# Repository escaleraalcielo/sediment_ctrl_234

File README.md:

# sediment_ctrl_234
 Repositorio en Github con todo el contenido relacionado con el rediseño de la trampa de sediemntos S/MT 234

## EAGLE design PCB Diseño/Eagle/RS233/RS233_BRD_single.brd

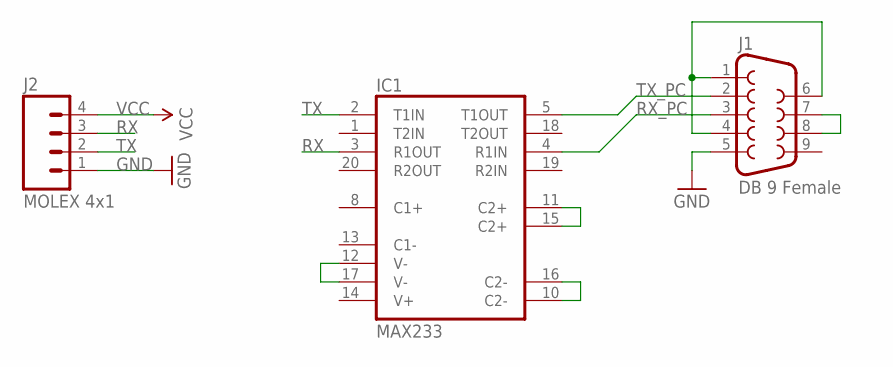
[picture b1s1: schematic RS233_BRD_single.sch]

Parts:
IC1: MAX233; DIL20
J1: DB 9 Female; DB9
J2: MOLEX 4x1; MOLEX-1X4

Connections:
GND: IC1.6 (GND), IC1.9 (GND), J1.5, J2.1
unnamed: IC1.11 (C2+), IC1.15 (C2+)
unnamed: IC1.10 (C2-), IC1.16 (C2-)
unnamed: J1.7, J1.8
unnamed: J1.1, J1.4, J1.6
unnamed: IC1.12 (V-), IC1.17 (V-)
RX: IC1.3 (R1OUT), J2.3
RX_PC: IC1.4 (R1IN), J1.3
TX: IC1.2 (T1IN), J2.2
TX_PC: IC1.5 (T1OUT), J1.2
VCC: IC1.7 (VCC), J2.4

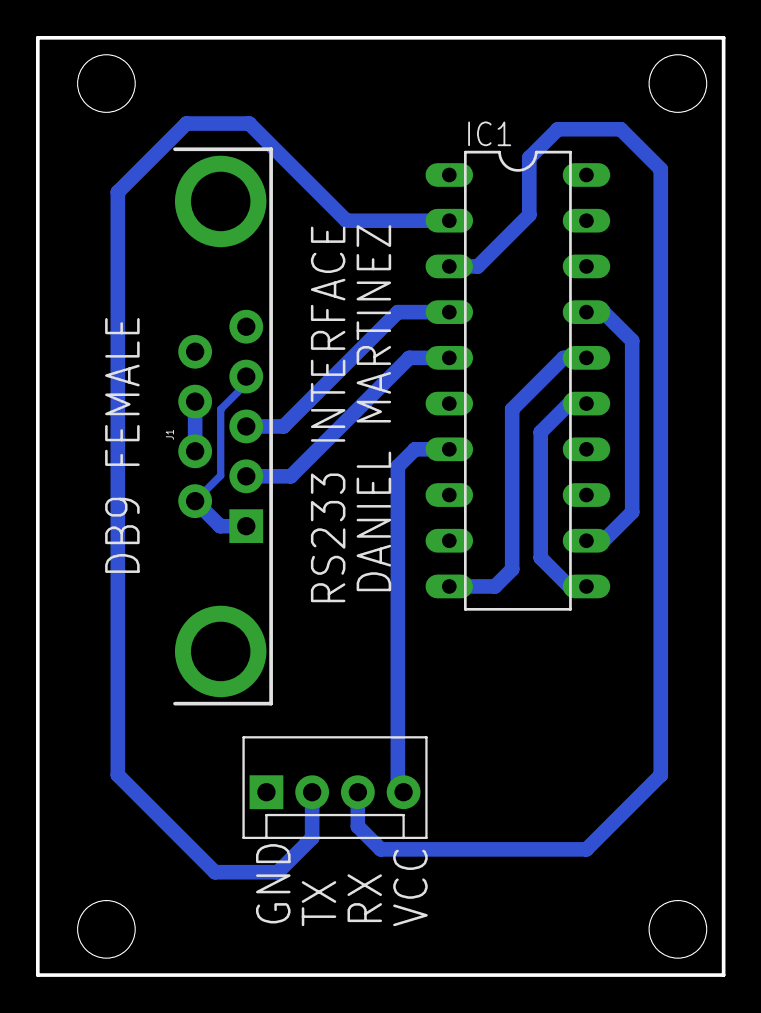
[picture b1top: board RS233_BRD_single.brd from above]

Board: 2 copper layers, 38.1 x 52.1 mm, 3 parts (0 on the bottom side), 11 nets.

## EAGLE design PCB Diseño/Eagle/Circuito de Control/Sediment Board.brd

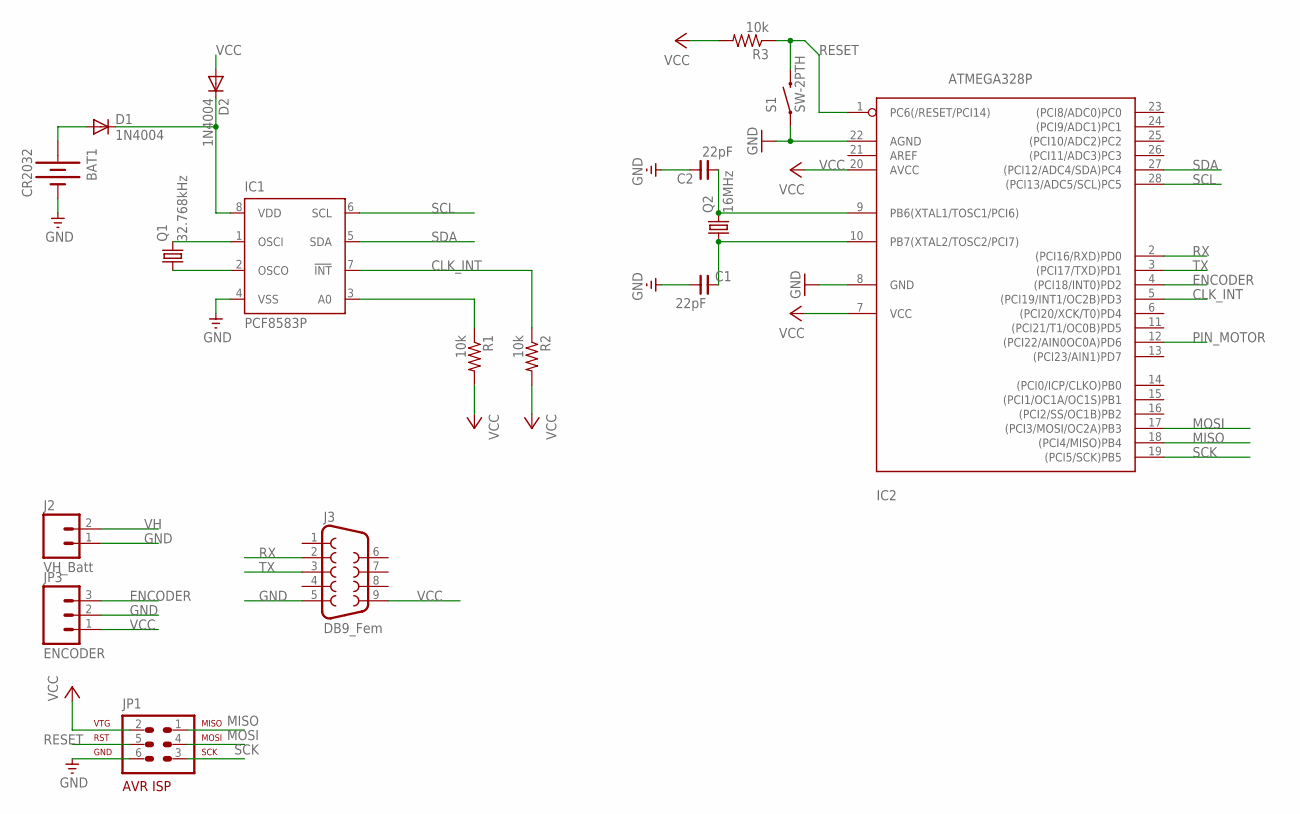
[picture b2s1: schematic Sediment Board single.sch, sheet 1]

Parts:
BAT1: CR2032; BATTCOM_20MM_PTH
C1, C2: 22pF; C025-050X025
D1, D2: 1N4004; DO41-10
IC1: PCF8583P; DIL08
IC2: ATMEGA328P; DIL28-3-ROUND
J2: VH_Batt; SCREWTERMINAL-3.5MM-2
J3: DB9_Fem; DB9
JP1: AVR-ISP-6
JP3: ENCODER; MOLEX-1X3
Q1: 32.768kHz; TC26H
Q2: 16MHz; HC49U70
R1, R2, R3: 10k; 0207/10
S1: SW-2PTH; TACTILE-PTH

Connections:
CLK_INT: IC1.7 (!INT), IC2.5 ((PCI19/INT1/OC2B)PD3), R2.1
ENCODER: IC2.4 ((PCI18/INT0)PD2), JP3.3
GND: BAT1.2 (-), C1.1, C2.2, IC1.4 (VSS), IC2.8 (GND), IC2.22 (AGND), J2.1, J3.5, JP1.6, JP3.2, S1.1; also elsewhere on the board
MISO: IC2.18 ((PCI4/MISO)PB4), JP1.1
MOSI: IC2.17 ((PCI3/MOSI/OC2A)PB3), JP1.4
unnamed: D1.C, D2.C, IC1.8 (VDD)
unnamed: IC1.1 (OSCI), Q1.2
unnamed: IC1.2 (OSCO), Q1.1
unnamed: BAT1.1 (+), D1.A
unnamed: IC1.3 (A0), R1.1
unnamed: C2.1, IC2.9 (PB6(XTAL1/TOSC1/PCI6)), Q2.2
unnamed: C1.2, IC2.10 (PB7(XTAL2/TOSC2/PCI7)), Q2.1
PIN_MOTOR: IC2.12 ((PCI22/AIN0OC0A)PD6); also elsewhere on the board
RESET: IC2.1 (PC6(/RESET/PCI14)), JP1.5, R3.1, S1.3 (2)
RX: IC2.2 ((PCI16/RXD)PD0), J3.2
SCK: IC2.19 ((PCI5/SCK)PB5), JP1.3
SCL: IC1.6 (SCL), IC2.28 ((PCI13/ADC5/SCL)PC5)
SDA: IC1.5 (SDA), IC2.27 ((PCI12/ADC4/SDA)PC4)
TX: IC2.3 ((PCI17/TXD)PD1), J3.3
VCC: D2.A, IC2.7 (VCC), IC2.20 (AVCC), J3.9, JP1.2, JP3.1, R1.2, R2.2, R3.2; also elsewhere on the board
VH: J2.2; also elsewhere on the board

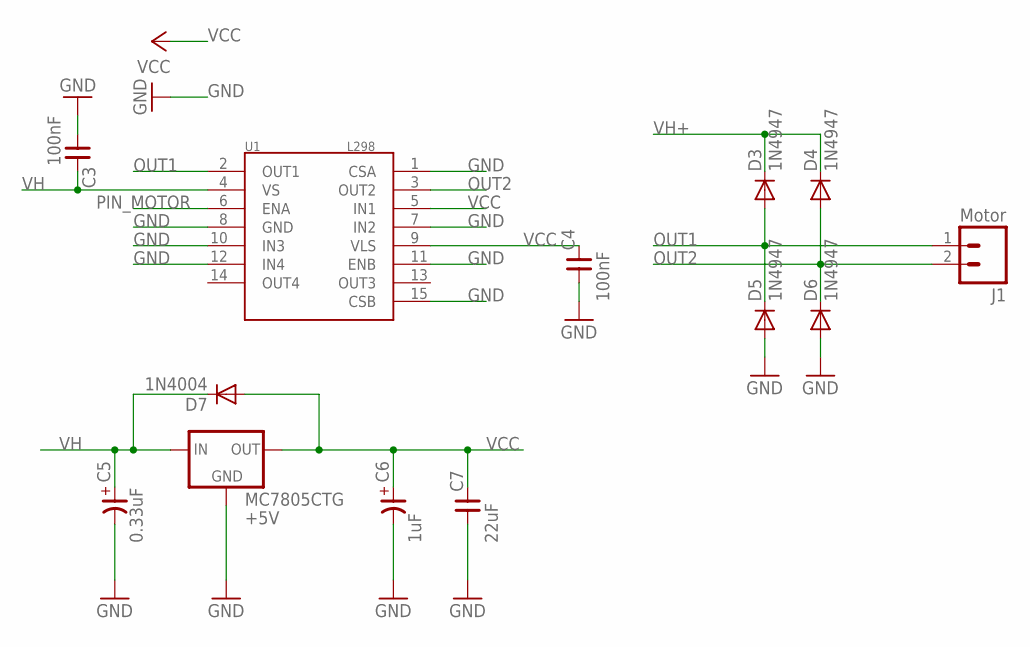
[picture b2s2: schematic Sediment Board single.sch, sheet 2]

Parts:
C3, C4: 100nF; C025-050X025
C5: 0.33uF; TT-025-040
C6: 1uF; TT-025-040
C7: 22uF; C025-050X025
D3, D4, D5, D6: 1N4947; DO41-10
D7: 1N4004; DO41-10
J1: Motor; SCREWTERMINAL-3.5MM-2
MC7805CTG: +5V; 78XXL
U1: L298; MULTIWATT15

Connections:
GND: C3.1, C4.1, C5.-, C6.-, C7.1, D5.A, D6.A, MC7805CTG.GND, U1.1 (CSA), U1.7 (IN2), U1.8 (GND), U1.10 (IN3), U1.11 (ENB), U1.12 (IN4), U1.15 (CSB); also elsewhere on the board
OUT1: D3.A, D5.C, J1.1, U1.2 (OUT1)
OUT2: D4.A, D6.C, J1.2, U1.3 (OUT2)
PIN_MOTOR: U1.6 (ENA); also elsewhere on the board
VCC: C4.2, C6.+, C7.2, D7.A, MC7805CTG.OUT, U1.5 (IN1), U1.9 (VLS); also elsewhere on the board
VH: C3.2, C5.+, D7.C, MC7805CTG.IN, U1.4 (VS); also elsewhere on the board
VH+: D3.C, D4.C

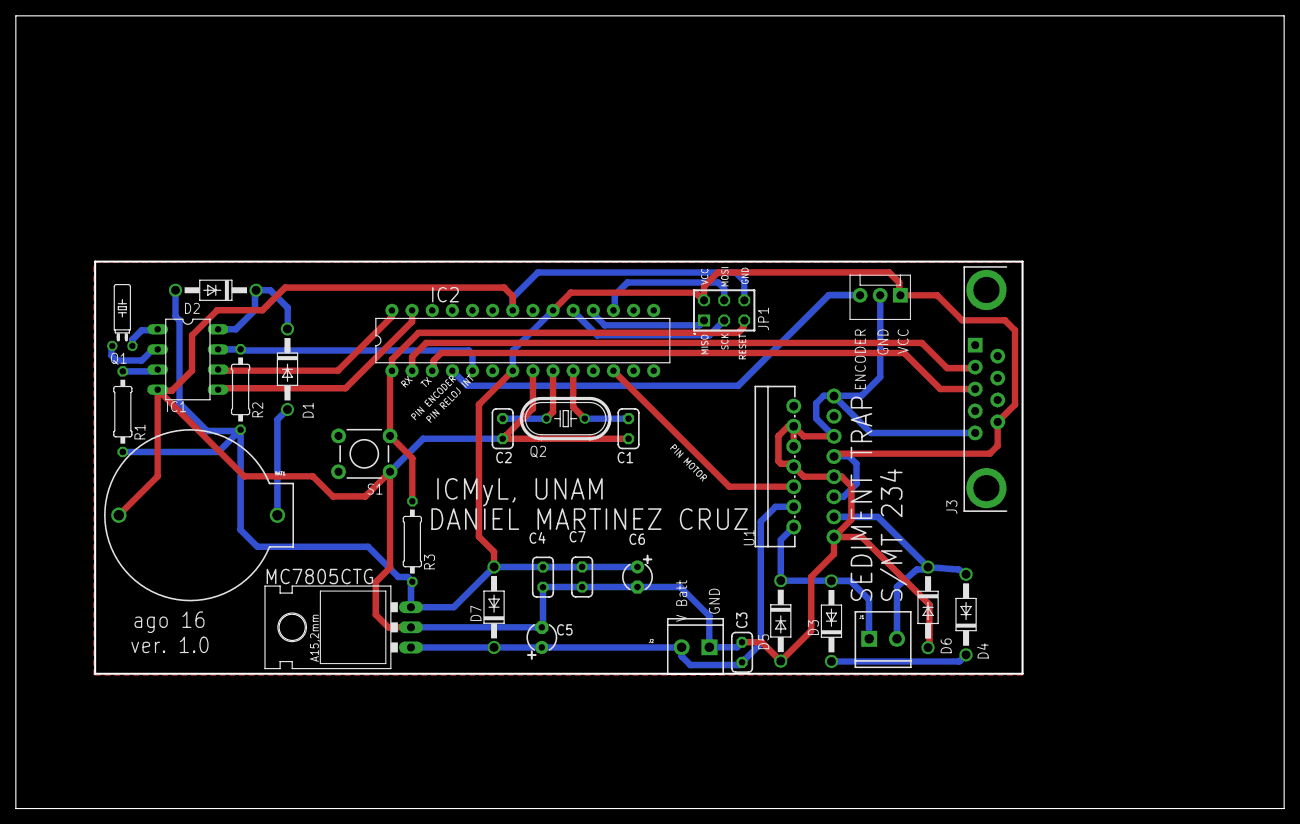
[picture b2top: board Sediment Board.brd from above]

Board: 2 copper layers, 159.7 x 99.7 mm, 32 parts (0 on the bottom side), 24 nets.

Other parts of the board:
FRAME1, FRAME2: FRAME-LETTER; CREATIVE_COMMONS

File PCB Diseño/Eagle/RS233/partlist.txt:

Partlist

Exported from Sediment Board.sch at 12/08/2016 09:30 p.m.

EAGLE Version 7.6.0 Copyright (c) 1988-2016 CadSoft

Assembly variant: 

Part     Value                 Device                Package               Library             Sheet

BAT1     CR2032                BATTERY20PTH          BATTCOM_20MM_PTH      SparkFun            1
C1       22pF                  CNP-C025-050X025      C025-050X025          cap-master          1
C2       22pF                  CNP-C025-050X025      C025-050X025          cap-master          1
C3       100nF                 CNP-C025-050X025      C025-050X025          cap-master          2
C4       100nF                 CNP-C025-050X025      C025-050X025          cap-master          2
D1       1N4004                1N4004                DO41-10               diode               1
D2       1N4004                1N4004                DO41-10               diode               1
D3       1N4947                1N4942                DO41-10               diode               2
D4       1N4947                1N4942                DO41-10               diode               2
D5       1N4947                1N4942                DO41-10               diode               2
D6       1N4947                1N4942                DO41-10               diode               2
IC1      PCF8583P              PCF8583P              DIL08                 ds1307_pcf8583      1
IC2      ATMEGA328PROUND       ATMEGA328PROUND       DIL28-3-ROUND         atmega328           1
J1                             M023.5MM              SCREWTERMINAL-3.5MM-2 SparkFun-Connectors 2
J2                             M023.5MM              SCREWTERMINAL-3.5MM-2 SparkFun-Connectors 1
JP1      AVR-ISP-6             AVR-ISP-6             AVR-ISP-6             atmel-1             1
JP3      ENCODER               M03POLAR              MOLEX-1X3             SparkFun            1
JP4      VCC                   M02POLAR              MOLEX-1X2             SparkFun            1
Q1       32.768kHz             CRYSTALTC26H          TC26H                 crystal             1
Q2       16MHz                 CRYSTALHC49U70        HC49U70               crystal             1
R1       10k                   R-US_0207/10          0207/10               resistor            1
R2       10k                   R-US_0207/10          0207/10               resistor            1
R3       10k                   R-US_0207/10          0207/10               resistor            1
S1       SWITCH-MOMENTARY-2PTH SWITCH-MOMENTARY-2PTH TACTILE-PTH           SparkFun            1
U$1      L298                  L298                  MULTIWATT15           SparkFun            2

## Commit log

2016-09-06 :octocat: Added .gitattributes & .gitignore files
2016-09-06 Archivos de PCB
2016-09-06 librería RTC PCF8583P
2016-09-06 Programa principal
2016-09-06 librería incorrecta
2016-09-06 Archivos GERBER generados correctamente
2016-09-10 Edición al 2016_09_09
2016-09-10 Eliminación para actualizar archivos
    Nuevos archivos generados
2016-09-10 actualización al 9 de septiembre
2016-10-05 edit
2016-10-05 deleted 16_10_05
2016-10-05 edited to 2016_10_05

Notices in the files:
parts and their libraries:
supply0: Copyright (C) 2007, Bob Starr
SparkFun-Connectors: Licensing: Creative Commons ShareAlike 4.0 International - https://creativecommons.org/licenses/by-sa/4.0
SparkFun-Aesthetics: Released under the Creative Commons Attribution Share-Alike 4.0 License
